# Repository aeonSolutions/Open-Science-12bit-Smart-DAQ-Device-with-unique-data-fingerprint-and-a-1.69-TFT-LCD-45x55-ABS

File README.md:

[ ](https://discord.gg/hw3j3RwfJf)

**Unique Visits** 

</p>

[PCB-Prototyping-Catalogue](https://github.com/aeonSolutions/PCB-Prototyping-Catalogue)  >>  [Laboratory Automation](https://github.com/aeonSolutions/PCB-Prototyping-Catalogue/tree/main/Laboratory%20Automation)  >>  [Smart DAQ](https://github.com/aeonSolutions/PCB-Prototyping-Catalogue/tree/main/Smart%20DAQ)  >> [12-bit Smart DAQs](https://github.com/aeonSolutions/PCB-Prototyping-Catalogue/tree/main/Smart%20DAQ/12-bit) >> 12-bit Smart DAQ Device with unique data fingerprint and a 1.69" TFT LCD  45x55 ABS

<br>

# 12bit Smart DAQ Device with unique data fingerprint and a 1.69" TFT LCD  45x55 ABS
This is the repository for revision of the 12-bit Smart DAQ Device with a unique data fingerprint able to do experimental data upload to any data repository. 

<br>

<p align="center">
<strong> <a href="https://aeonsolutions.github.io/sponsor/sdad/2ch/">Interactive view of the PCB Layout</a> </strong> &nbsp;
  <strong> <a href="https://aeonsolutions.github.io/sponsor/sdad/2ch/circuit_schematic.html">Interactive view of the circuit schematic</a> </strong> <br>
 <sup>Click to view the latest revision</sup>
</p>

<br>

Here one can find the following hardware electronics revisions:
- SDAD rev. 01-2023
- SDAD rev. 02-2023
- SDAD rev. 03-2023
- SDAD rev. 03-2023 B
- SDAD rev. 09-2023
- SDAD rev. 10-2023

####  Status: Tested. Require improvements. 

**Known faults:**
- PCB copper track optimizations
- components rearrangement for optimization of PCB track inductance 

<br>
 
## Dataverse API C library

This device uses my C++ library to expedite dataverse API integration on smart DAQ devices or elsewhere. Follow the link to its repository:

https://github.com/aeonSolutions/OpenScience-Dataverse-API-C-library

<p align="center">

</p>

<br>
<br>

The photo above is one of the many specimens I purposely fabricated to research self-sensing properties of asphalt mixed with a known content of carbon fibers. This is a 10cm cylinder specimen and on the top is already setup my own design smart #DAQ (get it here on my GitHub ) with the ability to upload LIVE experimental data to a #dataverse.

In the photo above the smart DAQ is installed on an acrylic case and screwed with plastic screws to an acrylic base with the same cross-section area as the specimen to be tested. 
The acrylic base can be bought [here](https://s.click.aliexpress.com/e/_DEGsZaL). And the acrylic case [here](https://s.click.aliexpress.com/e/_Dmudkjt). 

<br>

## CE Ready Logo
This hardware is ready to get a CE marking. To learn more about this marking goto to [Wikipedia here](https://en.wikipedia.org/wiki/CE_marking).

<br>

### Smart PCB Hardware Specifications
The hardware specifications for the 12bit pcb with dimensions of 23.5x43.5mm can be found [here](https://github.com/aeonSolutions/openScience-Smart-DAQ-to-Upload-Live-Experimental-Data-to-a-Data-Repository/wiki/Smart-DAQ-Specifications).

 **In real life this smart DAQ is able to:**
- connect to all kinds of 3V to 5V Digital sensors;
- connect to all kinds of sensors compatible with the I2C protocol. (max 118 sensors simultaneously)
- measure voltage in the range of  [0;3.3V]
- measure electrical resistance [0; 10^6] Ohm 
- do temperature and humidity compensation on all measurements 
- has a voltage reference sensor for improved accuracy on ADC measurements  
- has a motion sensor to know if anyone moved a specimen during an experiment
- ability to show live experimental data on the 1.69-inch TFT IPS LCD  

<br>
<br>

## PCB circuit Schematic 
The PCB circuit schematic is available in PDF located in the folder "PCB Schematic"
<br>

## KiCad project files
The project files in KiCad are located in the folder "KiCad".
<br>

<br>

## Proof of Concept

To test and validate proposed smart DAQ PCB electronics and its firmware as a solution for LIVE experimental data measurements on any test specimen part of a experimental campaign, This PCB electronics is being used to measure a predefined set of variables/parameters to further study several asphalt mixtures with known carbon fiber weight content in the asphalt matrix. Below is a YouTube link to an unedited short video showing one of the experimental setups.

<p align="center">
    <br>
 <sup>Video on Youtube</sup>
</p>

## Join the Beta Program
Join the beta program to test and debug to provide feedback, ideas, modifications, suggestions, improvements. And in return, write your own article blog or post on social media about it. See participation conditions on the [Wiki](https://github.com/aeonSolutions/PCB-Prototyping-Catalogue/wiki/Beta-Participation-Agreement).  

## Contributing

Bug reports and pull requests are welcome on any of AeonLabs repositories. This project is intended to be a safe, welcoming space for collaboration, and contributors are expected to adhere to the [code of conduct](https://github.com/aeonSolutions/OpenScience-Dataverse-API-C-library/blob/main/CODE_OF_CONDUCT.md).

- Contributing
  - [Your Contributions Matter](https://github.com/aeonSolutions/PCB-Prototyping-Catalogue/wiki/Your-Contributions-Matter)
  - [Contributor Code of Conduct](https://github.com/aeonSolutions/PCB-Prototyping-Catalogue/wiki/Contributor-Code-of-Conduct)

<br>

**[Beta Participation Agreement](https://github.com/aeonSolutions/PCB-Prototyping-Catalogue/wiki/Beta-Participation-Agreement)**

The Beta Participant Agreement is a legal document being executed between you and AeonLabs that outlines the conditions when participating in the Beta Program.

## Coding standards

Please make sure tests pass before committing, and add new tests for new additions.

- Licensing 
  - [AeonLabs Solutions for Open Hardware & Source Development](https://github.com/aeonSolutions/PCB-Prototyping-Catalogue/wiki/AeonLabs-Solutions-for-Open-Hardware-&-Source-Development)

<br>
<br>

## Author

You can get in touch with me on my LinkedIn Profile:

#### Miguel Tomas

You can also follow my GitHub Profile to stay updated about my latest projects: 

<br>

### Be supportive of my dedication and work towards technology education and buy me a cup of coffee
The PCB Desgin Files i provide here for anyone to use are free. If you like this Smart Device or use it, please consider buying me a cup of coffee, a slice of pizza or a book to help me study, eat and think new PCB design files.

<p align="center">
    
</p>

### Make a donation on Paypal
Make a donation on paypal and get a TAX refund*.

<p align="center">
    
</p>

### Support all these open hardware projects and become a Github sponsor  
Liked any of my PCB KiCad Designs? Help and Support my open work to all by becomming a Github sponsor.

<p align="center">

</p>

# 

### License

Before proceeding to download any of AeonLabs software solutions for open-source development and/or PCB hardware electronics development make sure you are choosing the right license for your project. See [AeonLabs Solutions for Open Hardware & Source Development](https://github.com/aeonSolutions/PCB-Prototyping-Catalogue/wiki/AeonLabs-Solutions-for-Open-Hardware-&-Source-Development) for more information.

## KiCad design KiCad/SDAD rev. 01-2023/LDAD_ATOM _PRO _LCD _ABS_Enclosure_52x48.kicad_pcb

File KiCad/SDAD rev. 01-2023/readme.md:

[PCB-Prototyping-Catalogue](https://github.com/aeonSolutions/PCB-Prototyping-Catalogue)  >>  [Laboratory Automation](https://github.com/aeonSolutions/PCB-Prototyping-Catalogue/tree/main/Laboratory%20Automation)  >>  [Smart DAQ](https://github.com/aeonSolutions/PCB-Prototyping-Catalogue/tree/main/Smart%20DAQ)  >> [12-bit Smart DAQs](https://github.com/aeonSolutions/PCB-Prototyping-Catalogue/tree/main/Smart%20DAQ/12-bit) >> 12-bit Smart DAQ Device with unique data fingerprint and a 1.69" TFT LCD  45x55 ABS

<div align="right">
 <a href="https://github-com.translate.goog/aeonSolutions/AeonLabs-AI-Volvo-MKII-Open-Hardware/wiki?_x_tr_sl=en&_x_tr_tl=pt&_x_tr_hl=en&_x_tr_pto=wapp">Change language</a>  <br>
Last change 05-03-2024
</div>

<br>

This folder contains the KiCad Project files, for the hardware electronics of the S.D.A.D.  Each KiCad project is available with a [creative commons share alike non-commercial license](https://creativecommons.org/licenses/by-nc-sa/4.0/deed.en) . 

<p align="center">
  <strong> <a href="https://aeonsolutions.github.io/sponsor/sdad/2ch/">Interactive web view of the PCB Layout</a> </strong> <br>
 <sup>Click to view the latest revision of the PCB Layout</sup>
</p>

If you like it and use it on your own hardware designs please support this project, [click here](https://github.com/sponsors/aeonSolutions) to learn how. <br> Thank you 🙏. 

### Support all these open hardware projects and become a GitHub sponsor  
Liked any of my PCB KiCad Designs? Help and Support my open work to all by becoming a GitHub sponsor.

<p align="center">

</p>

#

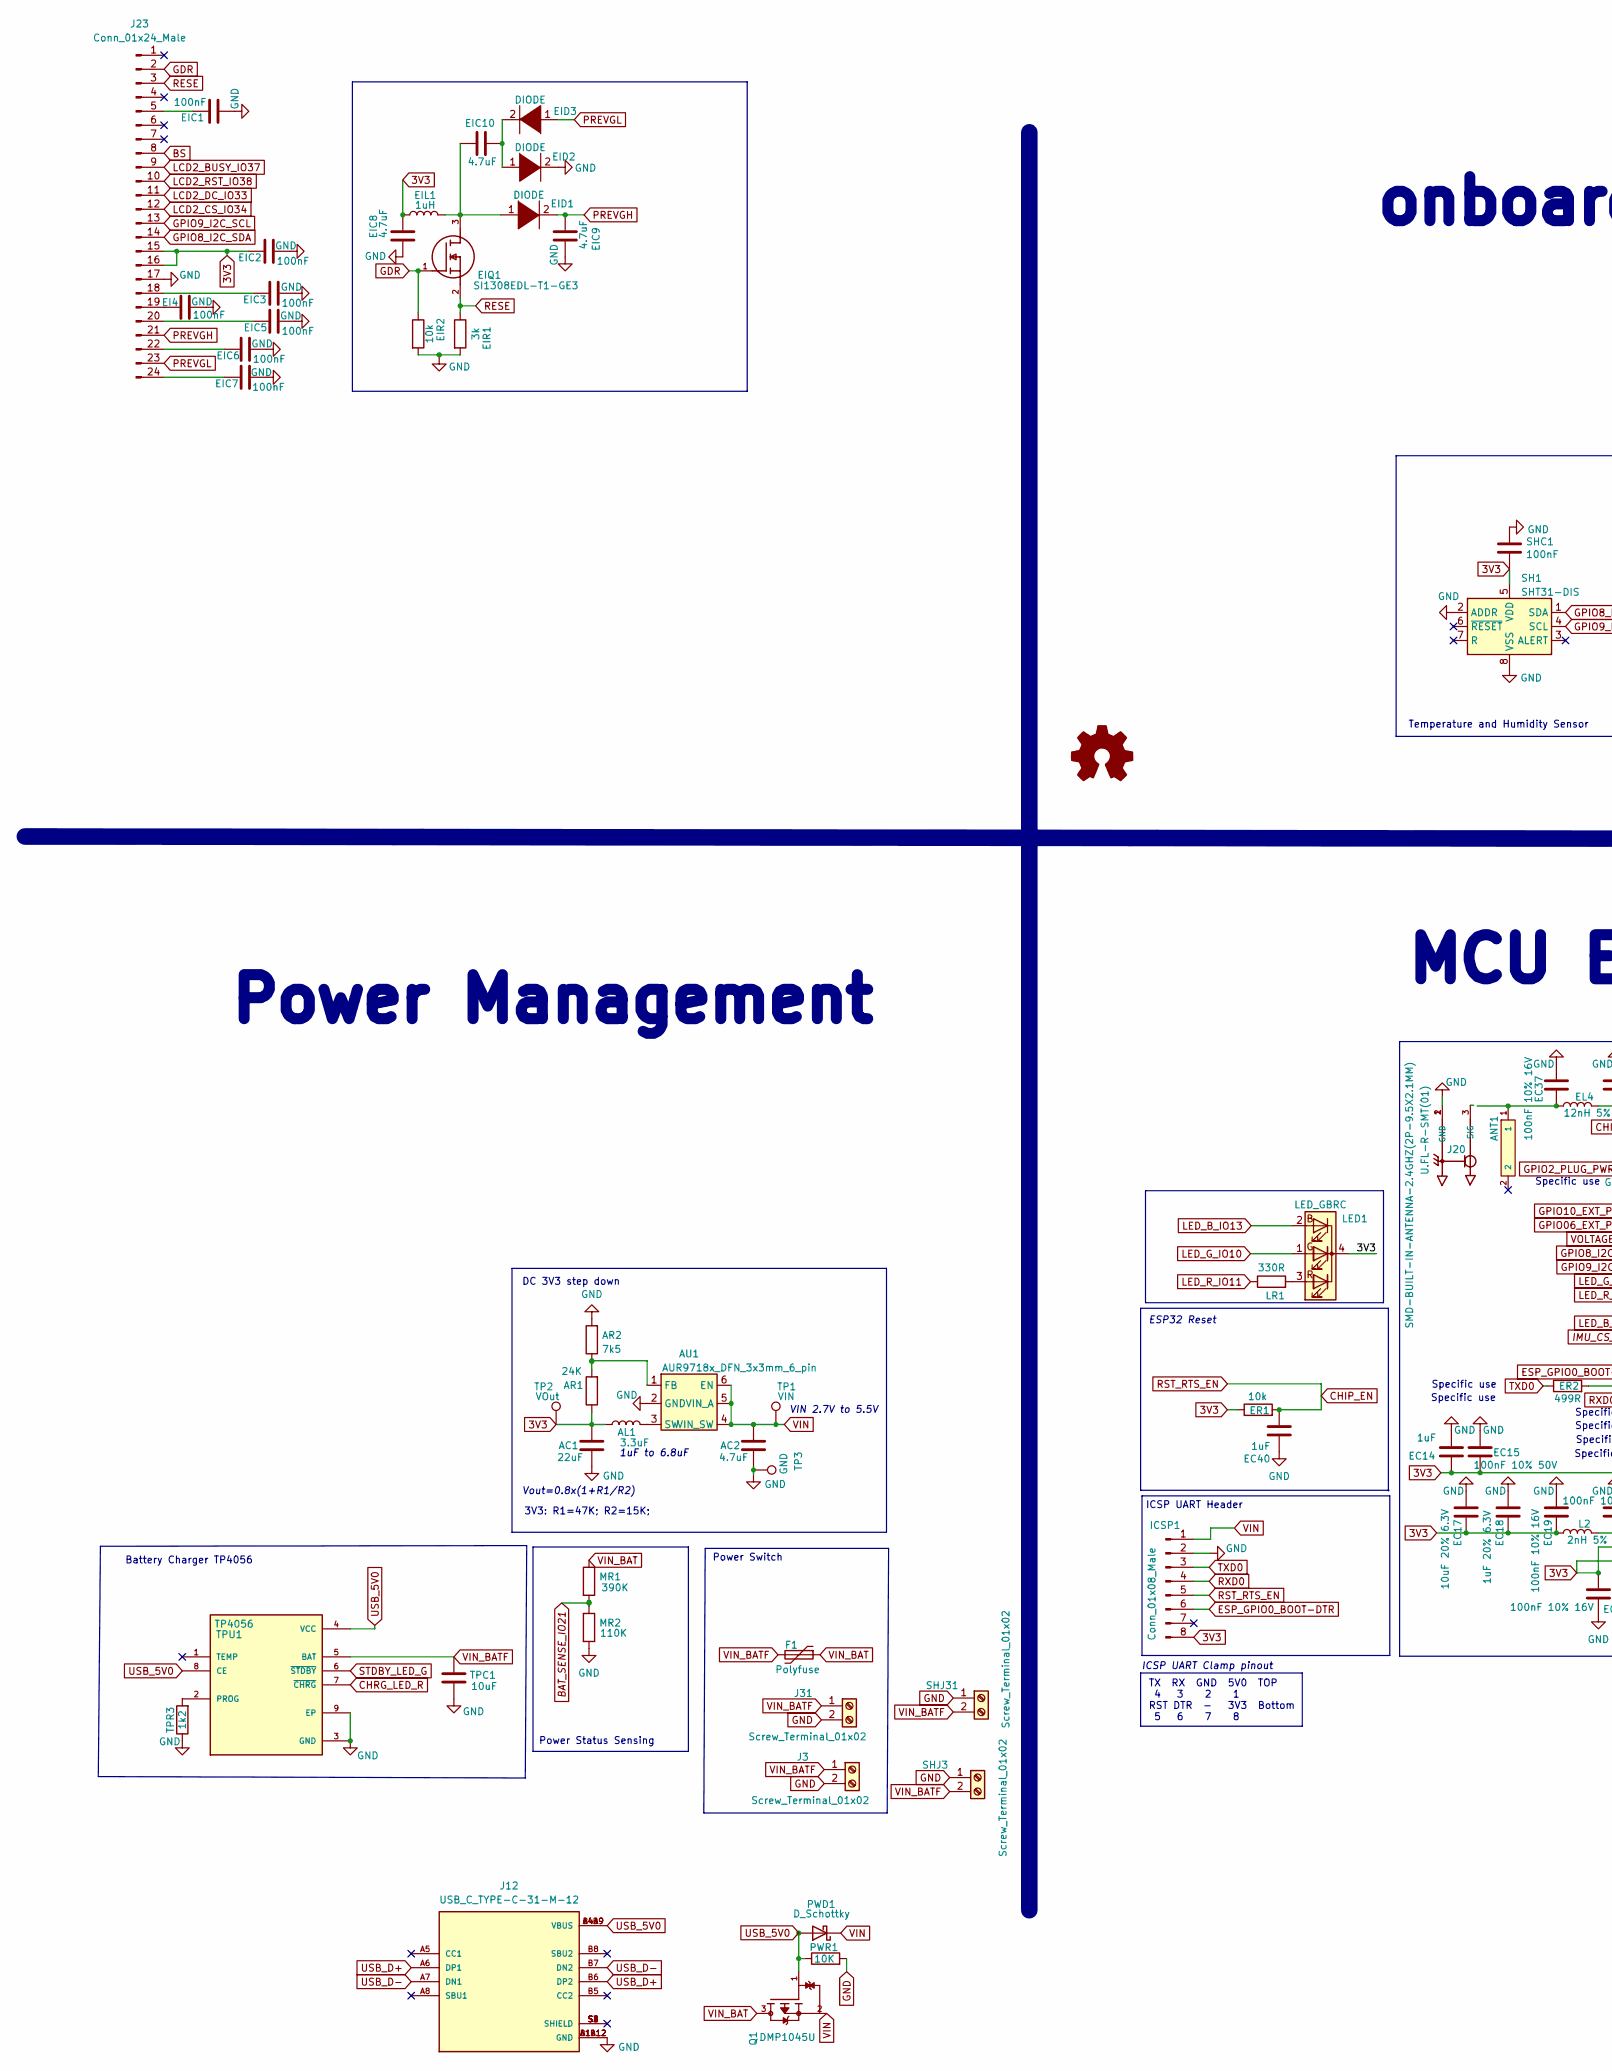
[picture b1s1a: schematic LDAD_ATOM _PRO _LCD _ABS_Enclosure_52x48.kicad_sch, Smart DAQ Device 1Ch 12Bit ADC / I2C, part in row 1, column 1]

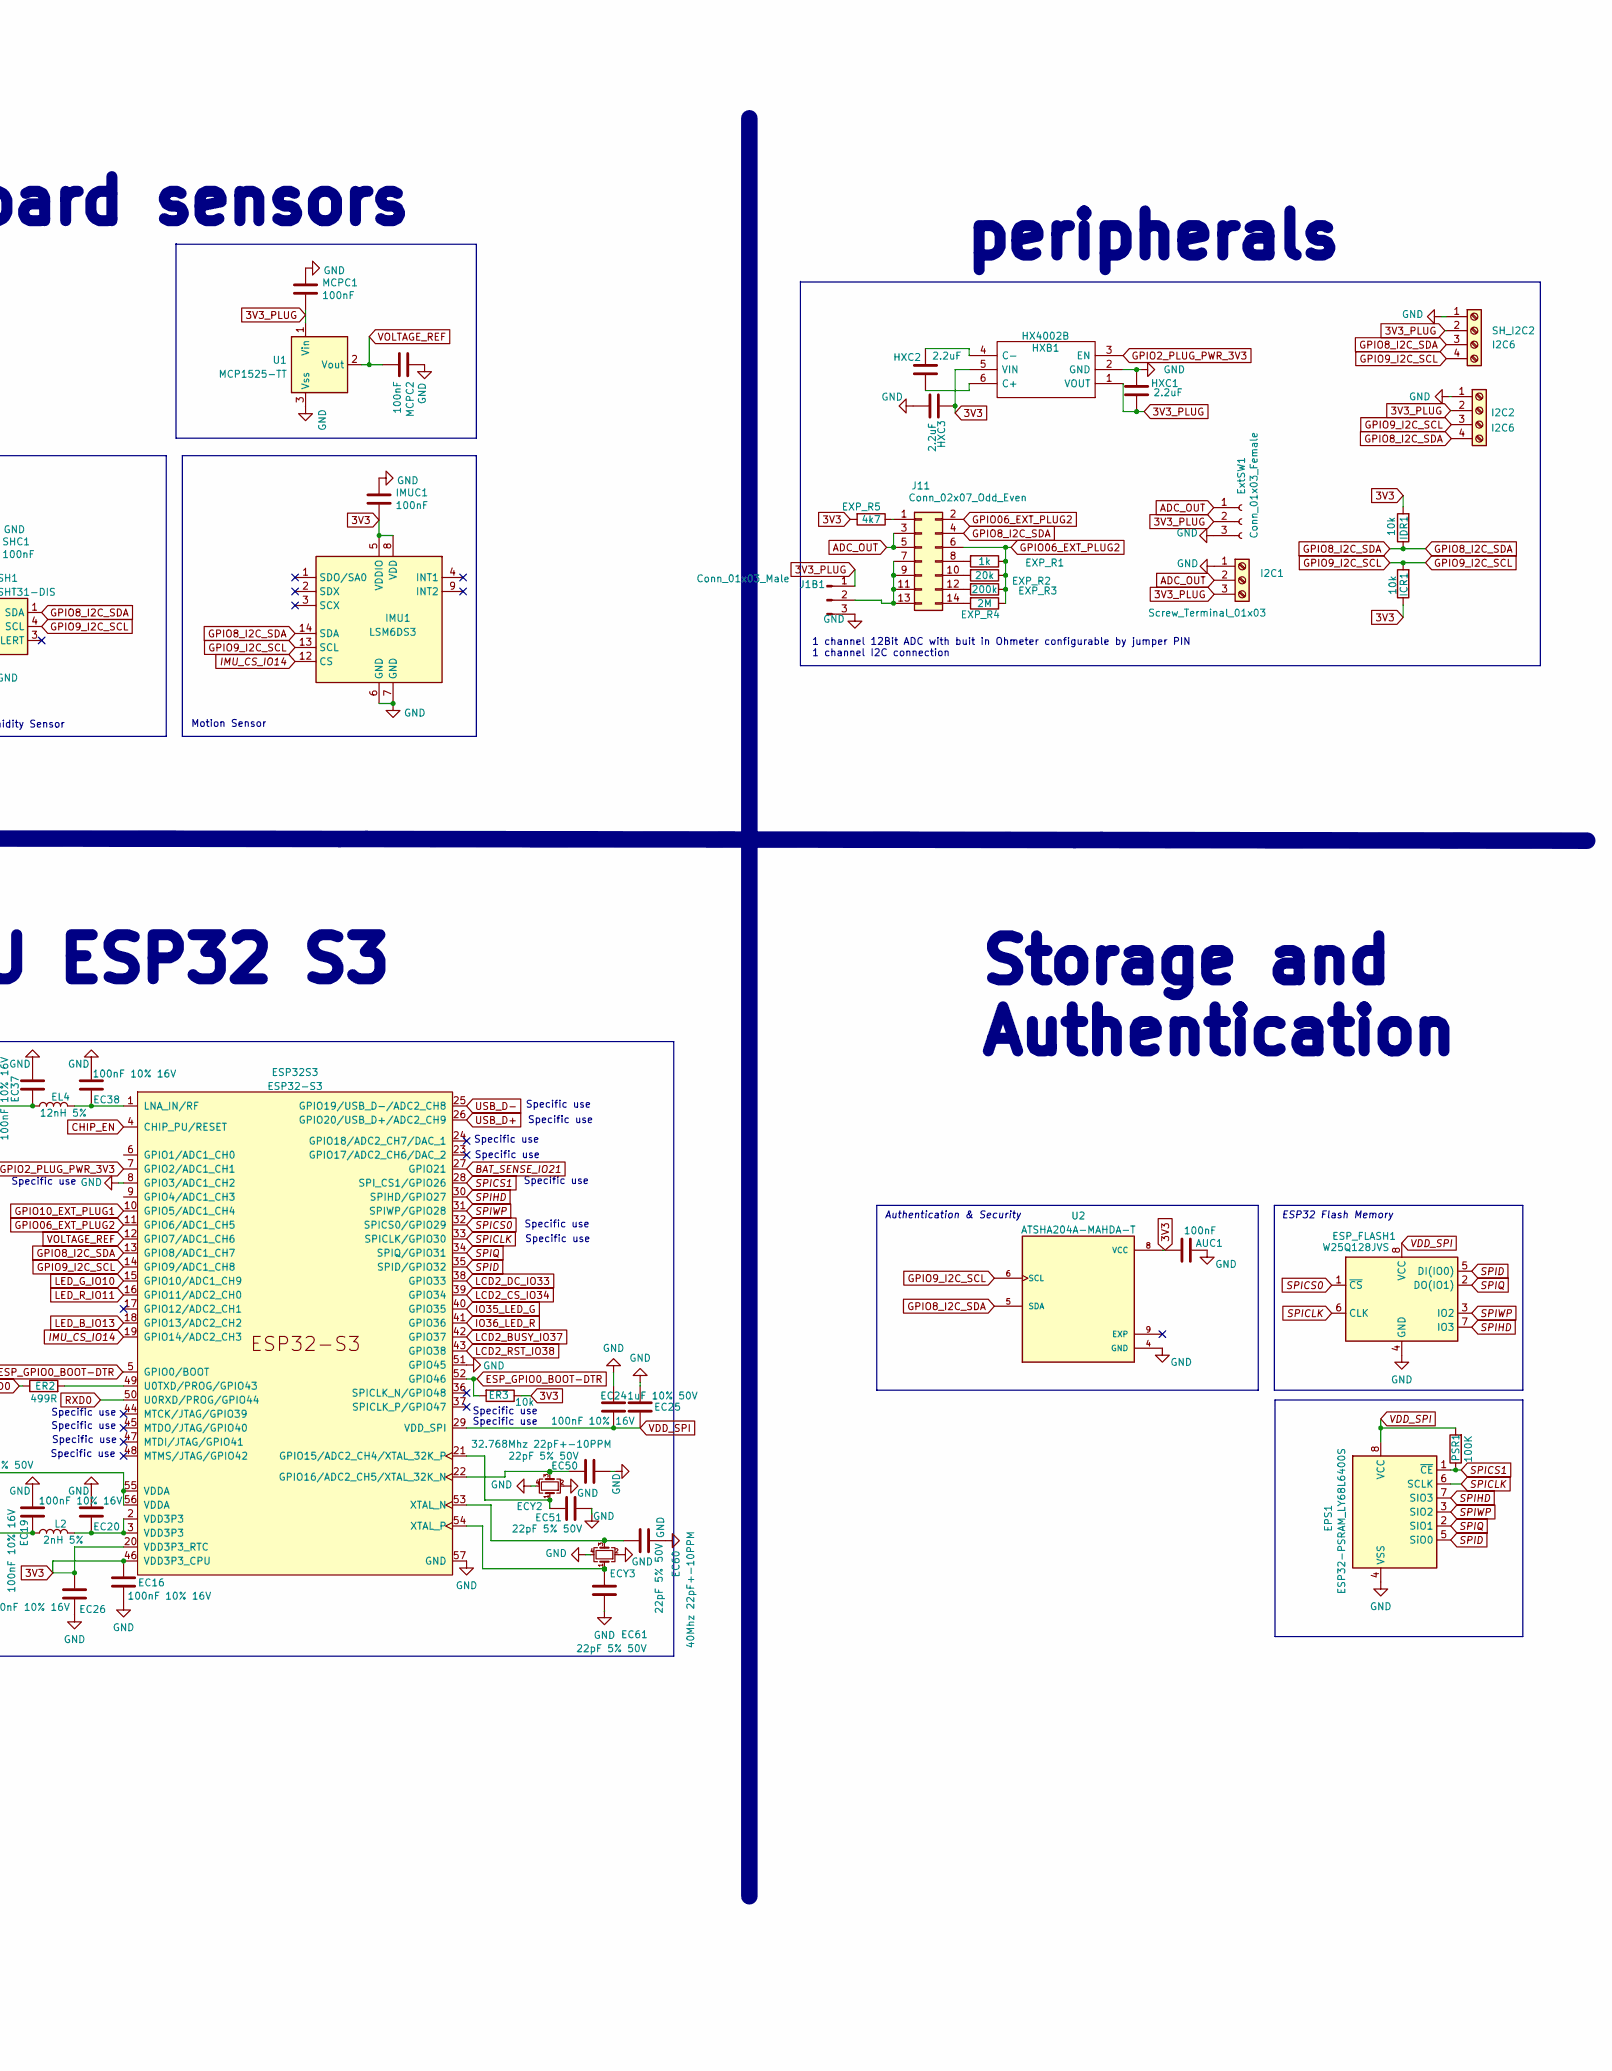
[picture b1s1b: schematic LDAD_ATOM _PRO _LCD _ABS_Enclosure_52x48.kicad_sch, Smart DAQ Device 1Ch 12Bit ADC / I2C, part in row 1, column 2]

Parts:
AC1: 22uF; C_0805_2012Metric_Pad1.18x1.45mm_HandSolder
AC2: 4.7uF; C_0805_2012Metric_Pad1.18x1.45mm_HandSolder
AL1: 3.3uF; L_1210_3225Metric
ANT1: SMD-BUILT-IN-ANTENNA-2.4GHZ(2P-9.5X2.1MM); AN9520_ANT2-SMD-9.5X2.1X1.0MM
AR1: 24K; R_0805_2012Metric_Pad1.20x1.40mm_HandSolder
AR2: 7k5; R_0805_2012Metric_Pad1.20x1.40mm_HandSolder
AU1: AUR9718x_DFN_3x3mm_6_pin; AUR9718 3x3mm 6 pin
AUC1: 100nF; C_0603_1608Metric
EC14, EC40: 1uF; C_0805_2012Metric
EC15: 100nF 10% 50V; C_0603_1608Metric
EC16, EC19, EC20, EC24, EC26, EC37, EC38: 100nF 10% 16V; C_0603_1608Metric
EC17: 10uF 20% 6.3V; C_0603_1608Metric
EC18: 1uF 20% 6.3V; C_0805_2012Metric
EC25: 1uF 10% 50V; C_0805_2012Metric
EC50, EC51, EC60, EC61: 22pF 5% 50V; C_0603_1608Metric
ECY2: 32.768Mhz 22pF+-10PPM; Crystal_SMD_EuroQuartz_MT-4Pin_3.2x2.5mm
ECY3: 40Mhz 22pF+-10PPM; Crystal_SMD_EuroQuartz_MT-4Pin_3.2x2.5mm
EI4: 100nF; C_0603_1608Metric
EIC1, EIC2, EIC3, EIC5, EIC6, EIC7: 100nF; C_0603_1608Metric
EIC8, EIC9, EIC10: 4.7uF; C_0603_1608Metric
EID1, EID2, EID3: DIODE; D_SOD-323
EIL1: 1uH; L_0805_2012Metric
EIQ1: SI1308EDL-T1-GE3; SOT-23; Mouser_Part_Number 78-SI1308EDL-T1-GE3
EIR1: 3k; R_0603_1608Metric
EIR2: 10k; R_0603_1608Metric
EL4: 12nH 5%; L_0805_2012Metric
EPS1: ESP32-PSRAM_LY68L6400S; SOIC-8_3.9x4.9mm_P1.27mm
ER1, ER3: 10k; R_0603_1608Metric
ER2: 499R; R_0603_1608Metric
ESP32S3: ESP32-S3; QFN-56-1EP_7x7mm_P0.4mm_EP5.6x5.6mm
ESP_FLASH1: W25Q128JVS; Flash SPI SON127P800X600X80-9N
EXP_R1: 1k; R_0603_1608Metric
EXP_R2: 20k; R_0603_1608Metric
EXP_R3: 200k; R_0603_1608Metric
EXP_R4: 2M; R_0603_1608Metric
EXP_R5: 4k7; R_0603_1608Metric
ExtSW1: Conn_01x03_Female; JST_SH_BM03B-SRSS-TB_1x03-1MP_P1.00mm_Vertical
F1: Polyfuse; Fuse_1206_3216Metric_Pad1.42x1.75mm_HandSolder
HXB1: HX4002B; HX4002 SOT95 P280X125-6N; Manufacturer_Part_Number HX4002
HXC1, HXC2, HXC3: 2.2uF; C_0603_1608Metric
I2C1: Screw_Terminal_01x03; JST_EH_B3B-EH-A_1x03_P2.50mm_Vertical
I2C2: I2C6; JST_EH_B4B-EH-A_1x04_P2.50mm_Vertical
ICR1: 10k; R_0603_1608Metric
ICSP1: Conn_01x08_Male; SOIC_clipProgSmall
IDR1: 10k; R_0603_1608Metric
IMU1: LSM6DS3; LSM6DS3 PQFN50P300X250X86-14N
IMUC1: 100nF; C_0603_1608Metric
J1B1: Conn_01x03_Male; PinHeader_1x03_P1.27mm_Vertical
J3, J31: Screw_Terminal_01x02; JST_EH_B2B-EH-A_1x02_P2.50mm_Vertical
J11: Conn_02x07_Odd_Even; PinHeader_2x07_P1.27mm_Vertical
J12: USB_C_TYPE-C-31-M-12; USB C HRO_TYPE-C-31-M-12; PARTREV A
J20: U.FL-R-SMT(01); HRS_U.FL-R-SMT(01)
J23: Conn_01x24_Male; 1.54 E-Ink 24 pin
L2: 2nH 5%; L_0805_2012Metric
LED1: LED_GBRC; LED_1206_3210_RGB_Metric
LR1: 330R; R_0603_1608Metric
MCPC1, MCPC2: 100nF; C_0603_1608Metric
MR1: 390K; R_0603_1608Metric
MR2: 110K; R_0603_1608Metric
PSR1: 100K; R_0603_1608Metric
PWD1: D_Schottky; D_1206_3216Metric
PWR1: 10K; R_0603_1608Metric
Q1: DMP1045U; SOT-23; PARTREV 7 - 2
SH1: SHT31-DIS; Sensirion_DFN-8-1EP_2.5x2.5mm_P0.5mm_EP1.1x1.7mm
SHC1: 100nF; C_0603_1608Metric
SHJ3, SHJ31: Screw_Terminal_01x02; JST_SH_SM02B-SRSS-TB_1x02-1MP_P1.00mm_Horizontal
SH_I2C2: I2C6; JST_SH_SM04B-SRSS-TB_1x04-1MP_P1.00mm_Horizontal
TP1: VIN; TestPoint_Pad_D1.0mm
TP2: VOut; TestPoint_Pad_D1.0mm
TP3: GND; TestPoint_Pad_D1.0mm
TPC1: 10uF; C_0805_2012Metric
TPR3: 1k2; R_0603_1608Metric
TPU1: TP4056
U1: MCP1525-TT; SOT-23
U2: ATSHA204A-MAHDA-T; ATSHA204A Auth SOIC8; PART_REV A

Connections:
3V3: AC1.1, AL1.1, AR1.1, AUC1.2, EC14.2, EC15.2, EC16.1, EC17.1, EC18.1, EC19.1, EC26.1, EIC2.1, EIC8.1, EIL1.1, ER1.1, ER3.1, ESP32S3.20 (VDD3P3_RTC), ESP32S3.46 (VDD3P3_CPU), ESP32S3.55 (VDDA), ESP32S3.56 (VDDA), EXP_R5.2, HXB1.5 (VIN), HXC3.2, ICR1.1, ICSP1.8, IDR1.2, IMU1.5 (VDDIO), IMU1.8 (VDD), IMUC1.2, J23.15, J23.16, L2.1, LED1.4 (K), SH1.5 (VDD), SHC1.2, TP2.1, U2.8 (VCC)
3V3_PLUG: ExtSW1.2, HXB1.1 (VOUT), HXC1.1, I2C1.3, I2C2.2, J1B1.1, MCPC1.2, SH_I2C2.2, U1.1 (Vin)
ADC_OUT: ExtSW1.1, I2C1.2, J11.3, J11.5
BAT_SENSE_IO21: ESP32S3.27 (GPIO21), MR1.2, MR2.1
BS: J23.8
CHIP_EN: EC40.2, ER1.2, ESP32S3.4 (CHIP_PU/RESET), ICSP1.5
CHRG_LED_R: TPU1.7 (~CHRG)
ESP_GPIO0_BOOT-DTR: ER3.2, ESP32S3.5 (GPIO0/BOOT), ESP32S3.52 (GPIO46), ICSP1.6
GDR: EIQ1.1, EIR2.1, J23.2
GND: AC1.2, AC2.2, AR2.2, AU1.2 (GND), AUC1.1, EC14.1, EC15.1, EC16.2, EC17.2, EC18.2, EC19.2, EC20.2, EC24.2, EC25.2, EC26.2, EC37.2, EC38.2, EC40.1, EC50.2, EC51.2, EC60.2, EC61.2, ECY2.2, ECY2.4, ECY3.2, ECY3.4, EI4.2, EIC1.2, EIC2.2, EIC3.2, EIC5.2, EIC6.2, EIC7.2, EIC8.2, EIC9.2, EID2.2 (A), EIR1.2, EIR2.2, EPS1.4 (VSS), ESP32S3.8 (GPIO3/ADC1_CH2), ESP32S3.51 (GPIO45), ESP32S3.57 (GND), ESP_FLASH1.4 (GND), ExtSW1.3, HXB1.2 (GND), HXC1.2, HXC3.1, I2C1.1, I2C2.1, ICSP1.2, IMU1.6 (GND), IMU1.7 (GND), IMUC1.1, J1B1.3, J3.2, J12.A1B12 (GND), J12.B1A12 (GND), J20.1 (GND), J20.2 (GND), J23.17, J31.2, MCPC1.1, MCPC2.1, MR2.2, PWR1.2, SH1.2 (ADDR), SH1.8 (VSS), SH1.9 (VSS), SHC1.1, SHJ3.1, SHJ31.1, SH_I2C2.1, TP3.1, TPC1.2, TPR3.1, TPU1.3 (GND), TPU1.9 (EP), U1.3 (Vss), U2.4 (GND)
GPIO2_PLUG_PWR_3V3: ESP32S3.7 (GPIO2/ADC1_CH1), HXB1.3 (EN)
GPIO06_EXT_PLUG2: ESP32S3.11 (GPIO6/ADC1_CH5), EXP_R1.1, EXP_R2.1, EXP_R3.1, EXP_R4.1, J11.2, J11.6
GPIO8_I2C_SDA: ESP32S3.13 (GPIO8/ADC1_CH7), I2C2.4, IDR1.1, IMU1.14 (SDA), J11.4, J23.14, SH1.1 (SDA), SH_I2C2.3, U2.5 (SDA)
GPIO9_I2C_SCL: ESP32S3.14 (GPIO9/ADC1_CH8), I2C2.3, ICR1.2, IMU1.13 (SCL), J23.13, SH1.4 (SCL), SH_I2C2.4, U2.6 (SCL)
GPIO10_EXT_PLUG1: ESP32S3.10 (GPIO5/ADC1_CH4)
IMU_CS_IO14: ESP32S3.19 (GPIO14/ADC2_CH3), IMU1.12 (CS)
IO35_LED_G: ESP32S3.40 (GPIO35)
IO36_LED_R: ESP32S3.41 (GPIO36)
LCD2_BUSY_IO37: ESP32S3.42 (GPIO37), J23.9
LCD2_CS_IO34: ESP32S3.39 (GPIO34), J23.12
LCD2_DC_IO33: ESP32S3.38 (GPIO33), J23.11
LCD2_RST_IO38: ESP32S3.43 (GPIO38), J23.10
LED_B_IO13: ESP32S3.18 (GPIO13/ADC2_CH2), LED1.2 (BA)
LED_G_IO10: ESP32S3.15 (GPIO10/ADC1_CH9), LED1.1 (GA)
LED_R_IO11: ESP32S3.16 (GPIO11/ADC2_CH0), LR1.1
unnamed: AL1.2, AU1.3 (SW)
unnamed: ANT1.1, EC37.1, EL4.1
unnamed: AR1.2, AR2.1, AU1.1 (FB)
unnamed: EC20.1, ESP32S3.2 (VDD3P3), ESP32S3.3 (VDD3P3), L2.2
unnamed: EC38.1, EL4.2, ESP32S3.1 (LNA_IN/RF)
unnamed: EC50.1, ECY2.3, ESP32S3.22 (GPIO16/ADC2_CH5/XTAL_32K_N)
unnamed: EC51.1, ECY2.1, ESP32S3.21 (GPIO15/ADC2_CH4/XTAL_32K_P)
unnamed: EC60.1, ECY3.3, ESP32S3.53 (XTAL_N)
unnamed: EC61.1, ECY3.1, ESP32S3.54 (XTAL_P)
unnamed: EI4.1, J23.19
unnamed: EIC1.1, J23.5
unnamed: EIC3.1, J23.18
unnamed: EIC5.1, J23.20
unnamed: EIC6.1, J23.22
unnamed: EIC7.1, J23.24
unnamed: EIC10.1, EID2.1 (K), EID3.2 (A)
unnamed: EIC10.2, EID1.1 (K), EIL1.2, EIQ1.3
unnamed: ER2.2, ESP32S3.49 (U0TXD/PROG/GPIO43)
unnamed: EXP_R1.2, J11.8
unnamed: EXP_R2.2, J11.10
unnamed: EXP_R3.2, J11.12
unnamed: EXP_R4.2, J11.14
unnamed: EXP_R5.1, J11.1
unnamed: HXB1.4 (C-), HXC2.2
unnamed: HXB1.6 (C+), HXC2.1
unnamed: J1B1.2, J11.7, J11.9, J11.11, J11.13
unnamed: LED1.3 (RA), LR1.2
unnamed: TPR3.2, TPU1.2 (PROG)
PREVGH: EIC9.1, EID1.2 (A), J23.21
PREVGL: EID3.1 (K), J23.23
RESE: EIQ1.2, EIR1.1, J23.3
RXD0: ESP32S3.50 (U0RXD/PROG/GPIO44), ICSP1.4
SPICLK: EPS1.6 (SCLK), ESP32S3.33 (SPICLK/GPIO30), ESP_FLASH1.6 (CLK)
SPICS0: ESP32S3.32 (SPICS0/GPIO29), ESP_FLASH1.1 (~CS)
SPICS1: EPS1.1 (~CE), ESP32S3.28 (SPI_CS1/GPIO26), PSR1.1
SPID: EPS1.5 (SiO0), ESP32S3.35 (SPID/GPIO32), ESP_FLASH1.5 (DI(IO0))
SPIHD: EPS1.7 (SIO3), ESP32S3.30 (SPIHD/GPIO27), ESP_FLASH1.7 (IO3)
SPIQ: EPS1.2 (SIO1), ESP32S3.34 (SPIQ/GPIO31), ESP_FLASH1.2 (DO(IO1))
SPIWP: EPS1.3 (SIO2), ESP32S3.31 (SPIWP/GPIO28), ESP_FLASH1.3 (IO2)
STDBY_LED_G: TPU1.6 (~STDBY)
TXD0: ER2.1, ICSP1.3
USB_5V0: J12.A4B9 (VBUS), J12.B4A9 (VBUS), PWD1.2 (A), PWR1.1, Q1.1, TPU1.4 (VCC), TPU1.8 (CE)
USB_D+: ESP32S3.26 (GPIO20/USB_D+/ADC2_CH9), J12.A6 (DP1), J12.B6 (DP2)
USB_D-: ESP32S3.25 (GPIO19/USB_D-/ADC2_CH8), J12.A7 (DN1), J12.B7 (DN2)
VDD_SPI: EC24.1, EC25.1, EPS1.8 (VCC), ESP32S3.29 (VDD_SPI), ESP_FLASH1.8 (VCC), PSR1.2
VIN: AC2.1, AU1.4 (VIN_SW), AU1.5 (VIN_A), AU1.6 (EN), ICSP1.1, PWD1.1 (K), Q1.2, TP1.1
VIN_BAT: F1.1, MR1.1, Q1.3
VIN_BATF: F1.2, J3.1, J31.1, SHJ3.2, SHJ31.2, TPC1.1, TPU1.5 (BAT)
VOLTAGE_REF: ESP32S3.12 (GPIO7/ADC1_CH6), MCPC2.2, U1.2 (Vout)

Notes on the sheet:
Specific use
3V3: R1=47K; R2=15K;
ICSP UART Header
peripherals
Vout=0.8x(1+R1/R2)
ESP32 Flash Memory
DC 3V3 step down
ESP32 Reset
Temperature and Humidity Sensor
1uF to 6.8uF
Motion Sensor
1 channel 12Bit ADC with buit in Ohmeter configurable by jumper PIN 1 channel I2C connection
onboard sensors
ICSP UART Clamp pinout
Storage and Authentication
Battery Charger TP4056
Power Management
Authentication & Security
VIN 2.7V to 5.5V
Power Switch
MCU ESP32 S3
TX RX GND 5V0 TOP 4 3 2 1 RST DTR - 3V3 Bottom 5 6 7 8
Power Status Sensing

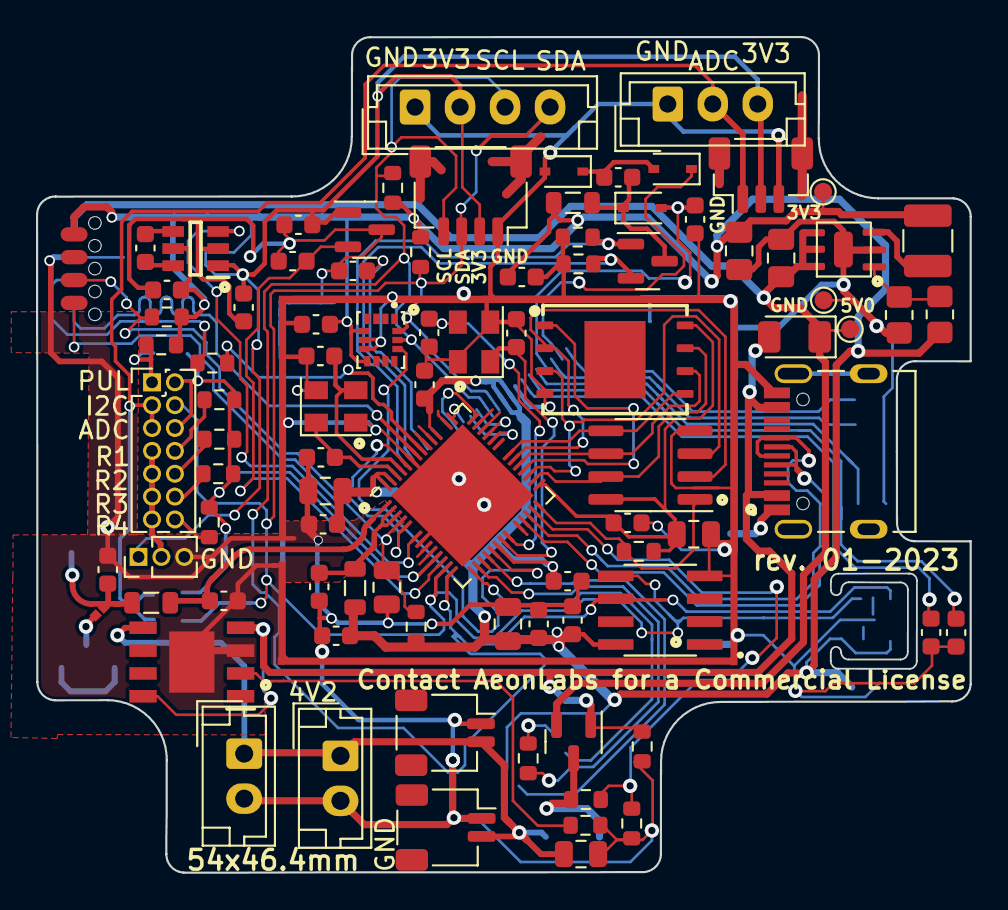
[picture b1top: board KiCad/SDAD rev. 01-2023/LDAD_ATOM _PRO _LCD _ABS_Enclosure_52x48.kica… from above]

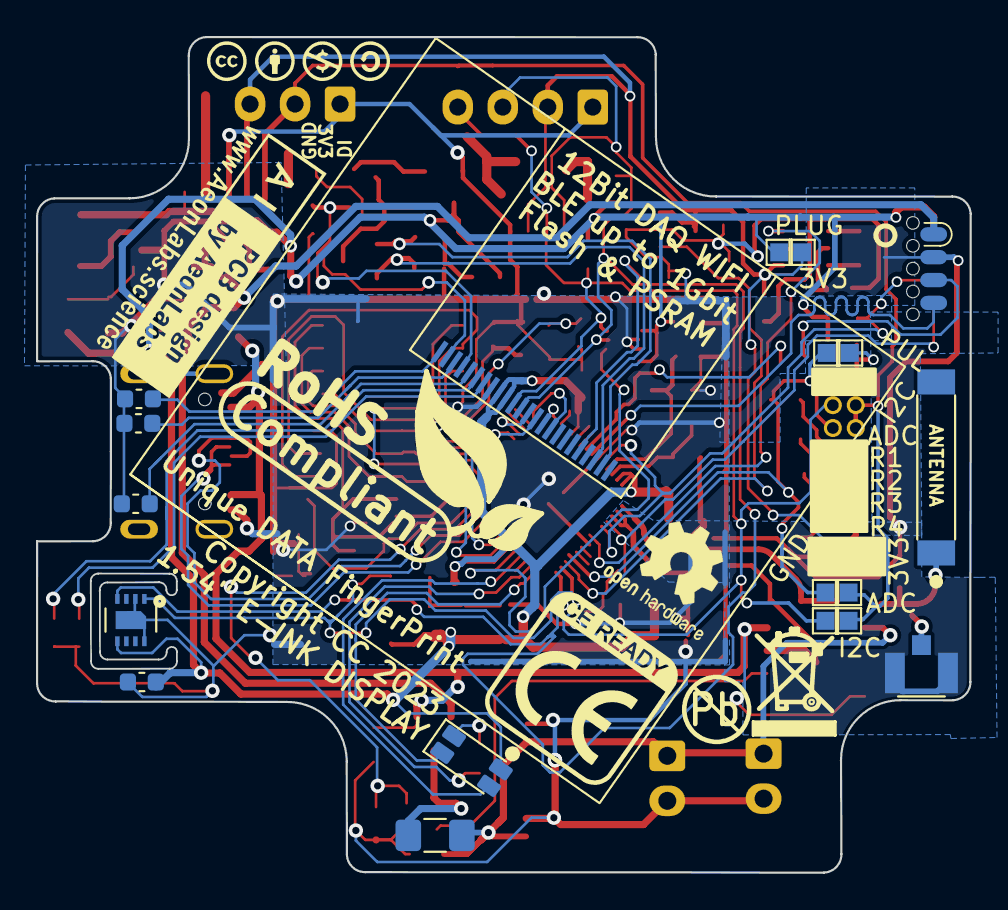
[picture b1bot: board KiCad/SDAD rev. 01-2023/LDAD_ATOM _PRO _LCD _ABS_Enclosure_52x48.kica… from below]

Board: 2 copper layers, 51.9 x 46.4 mm, 102 parts (14 on the bottom side), 68 nets.

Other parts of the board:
Sign-PbFree: LOGO_PBFREE
Sign-RecycleBin: LOGO_RECYCLEBIN_1
Sign-RoHS: LOGO_ROHS_1

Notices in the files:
KiCad/SDAD rev. 01-2023/LDAD_ATOM _PRO _LCD _ABS_Enclosure_52x48.kicad_pcb:
Copyright CC 2023
